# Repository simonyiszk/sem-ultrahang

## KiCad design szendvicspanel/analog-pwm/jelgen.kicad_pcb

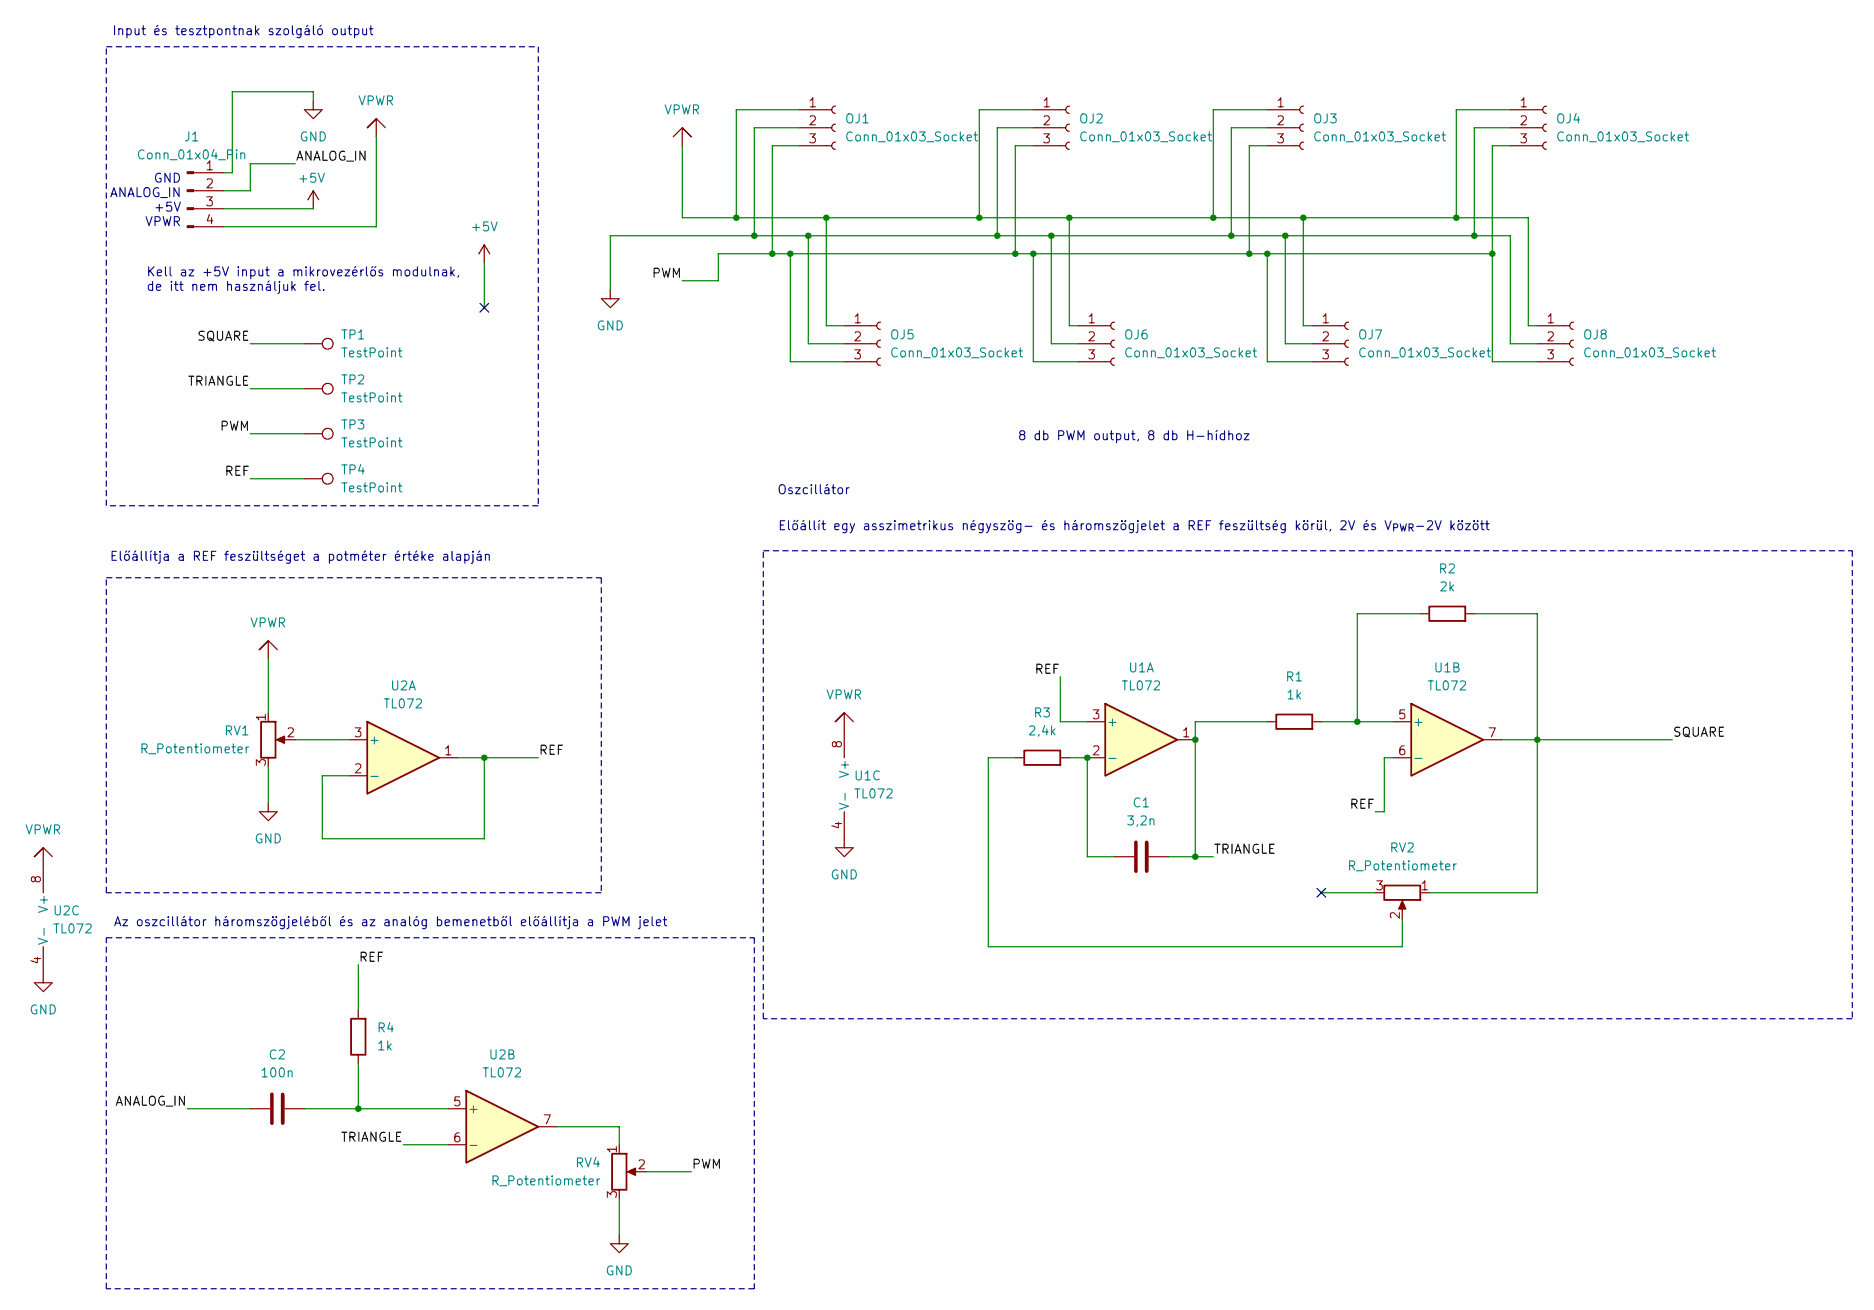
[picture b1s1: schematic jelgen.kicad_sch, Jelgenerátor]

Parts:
C1: 3,2n; C_Axial_L5.1mm_D3.1mm_P7.50mm_Horizontal
C2: 100n; C_Axial_L5.1mm_D3.1mm_P7.50mm_Horizontal
J1: Conn_01x04_Pin; PinHeader_1x04_P2.54mm_Horizontal
OJ1, OJ2, OJ3, OJ4, OJ5, OJ6, OJ7, OJ8: Conn_01x03_Socket; PinSocket_1x03_P2.54mm_Vertical
R1, R4: 1k; R_Axial_DIN0204_L3.6mm_D1.6mm_P5.08mm_Horizontal
R2: 2k; R_Axial_DIN0204_L3.6mm_D1.6mm_P5.08mm_Horizontal
R3: 2,4k; R_Axial_DIN0204_L3.6mm_D1.6mm_P5.08mm_Horizontal
RV1, RV2, RV4: R_Potentiometer; Potentiometer_Bourns_3266Y_Vertical
TP1, TP2, TP3, TP4: TestPoint; PinHeader_1x01_P2.54mm_Vertical
U1, U2: TL072; DIP-8_W7.62mm

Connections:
+5V: J1.3
/ANALOG_IN: C2.1, J1.2
/PWM: OJ1.3, OJ2.3, OJ3.3, OJ4.3, OJ5.3, OJ6.3, OJ7.3, OJ8.3, RV4.2, TP3.1
/REF: R4.2, TP4.1, U1.3 (+), U1.6 (-), U2.1, U2.2 (-)
/SQUARE: R2.2, RV2.1, TP1.1, U1.7
/TRIANGLE: C1.2, R1.1, TP2.1, U1.1, U2.6 (-)
GND: J1.1, OJ1.2, OJ2.2, OJ3.2, OJ4.2, OJ5.2, OJ6.2, OJ7.2, OJ8.2, RV1.3, RV4.3, U1.4 (V-), U2.4 (V-)
unnamed: R3.1, RV2.2
unnamed: RV4.1, U2.7
unnamed: C1.1, R3.2, U1.2 (-)
unnamed: R1.2, R2.1, U1.5 (+)
unnamed: RV1.2, U2.3 (+)
unnamed: C2.2, R4.1, U2.5 (+)
VPWR: J1.4, OJ1.1, OJ2.1, OJ3.1, OJ4.1, OJ5.1, OJ6.1, OJ7.1, OJ8.1, RV1.1, U1.8 (V+), U2.8 (V+)

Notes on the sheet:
Input és tesztpontnak szolgáló output
GND ANALOG_IN +5V VPWR
Az oszcillátor háromszögjeléből és az analóg bemenetből előállítja a PWM jelet
Előállít egy asszimetrikus négyszög- és háromszögjelet a REF feszültség körül, 2V és V_{PWR}-2V között
Előállítja a REF feszültséget a potméter értéke alapján
Kell az +5V input a mikrovezérlős modulnak, de itt nem használjuk fel.
8 db PWM output, 8 db H-hídhoz
Oszcillátor

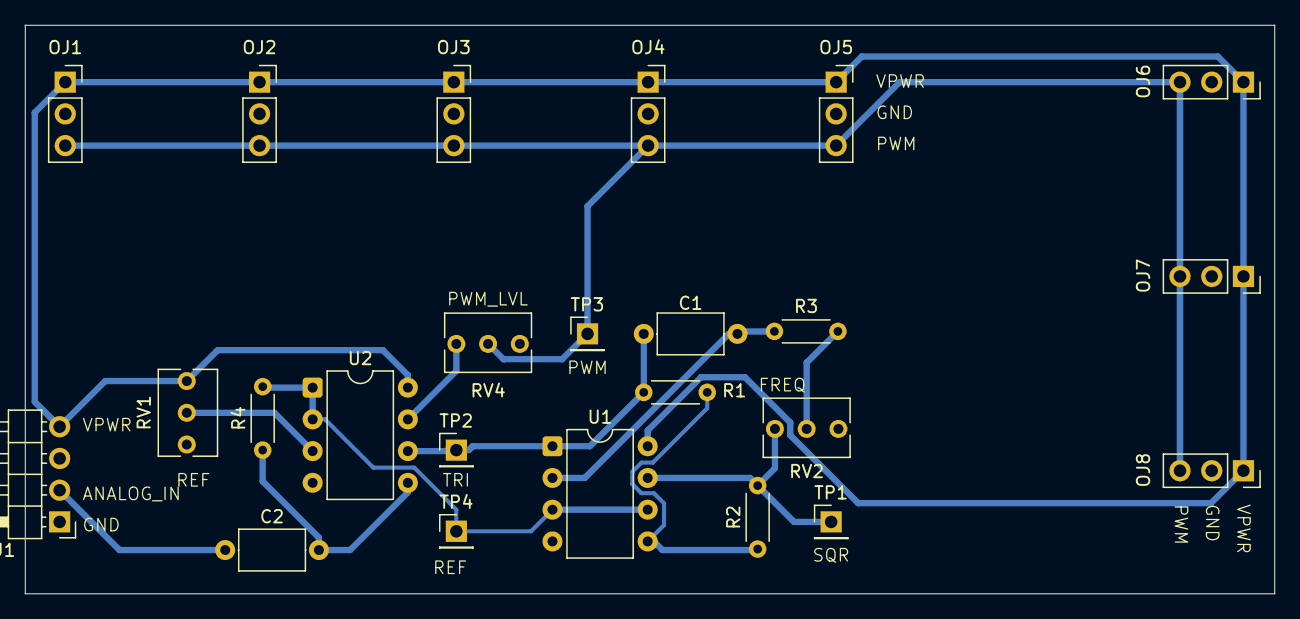
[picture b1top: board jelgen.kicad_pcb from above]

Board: 2 copper layers, 100.0 x 45.5 mm, 24 parts (0 on the bottom side), 13 nets.
